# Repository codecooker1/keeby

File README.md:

# keeby
A custom ergonomic split keyboard made for HackClub Blueprint based on Corne, Lily58 and Sofle V2

# Routing PCB
more detailed svg and pdf available in PCB/plot

# Schematic for the right half

# Schematic for the left half

# Casing??
Yup, made the casing in onshape. This is supposed to be 3D printed. You can find the 3D part files in the CAD/PrintParts folder. Here the FullCase is the full 3D model of the casing all parts included. Or you can find 3D models of individual parts in the CAD/PrintParts folder named by part.

Alternatively, you can view the Onshape design here: https://cad.onshape.com/documents/7252c9cab477090fa80b5ebe/w/9b87afb059b10e97f9e15540/e/26e119e6690b400aabda07c5

# How does the final PCB looks?

For detailed view the .step files is in PCB/3dout/

# Final Assembled Keyboard

# Detailed BOM of Keeby

|    | Sourced | Placed | References                                                                                                                                                                                                                                                                                                                                        | Value                | Footprint                               | Description                                                             | Quantity | Unit Price | Total Price | Link                                                                                                                                                                                                                                                                                                                                                                                                                                                                                                                                                                                                                                                                                                                                                                                                                                                                                                                                                                                                                                                                              |
|----|---------|--------|---------------------------------------------------------------------------------------------------------------------------------------------------------------------------------------------------------------------------------------------------------------------------------------------------------------------------------------------------|----------------------|-----------------------------------------|-------------------------------------------------------------------------|----------|------------|-------------|-----------------------------------------------------------------------------------------------------------------------------------------------------------------------------------------------------------------------------------------------------------------------------------------------------------------------------------------------------------------------------------------------------------------------------------------------------------------------------------------------------------------------------------------------------------------------------------------------------------------------------------------------------------------------------------------------------------------------------------------------------------------------------------------------------------------------------------------------------------------------------------------------------------------------------------------------------------------------------------------------------------------------------------------------------------------------------------|
| 1  |         |        | L*                                                           | SK6812MINI-E         | LED_choc_6028R-ROT                      | Reverse mount adressable LED (WS2812 protocol) SK6812-MINI-E            | 58       |            | $6.19       | https://www.aliexpress.com/item/1005007863635868.html?spm=a2g0o.cart.0.0.810538darhu6L5&mp=1&pdp_npi=6%40dis%21USD%21USD%206.19%21USD%206.19%21%21USD%206.19%21%21%21%40212a70c017685672603975784e0c90%2112000042594617264%21ct%21BD%216073142226%21%211%210%21                                                                                                                                                                                                                                                                                                                                                                                                                                                                                                                                                                                                                                                                                                                                                                                                                   |
| 2  |         |        | D*                                                           | D                    | D_SOD-123                               | Diode                                                                   | 100      |            | $0.90       | https://www.aliexpress.com/item/1005005460442161.html?spm=a2g0o.cart.0.0.810538darhu6L5&mp=1&pdp_npi=6%40dis%21USD%21USD%200.98%21USD%200.86%21%21USD%200.86%21%21%21%40212a70c017685672603975784e0c90%2112000033171824002%21ct%21BD%216073142226%21%211%210%21                                                                                                                                                                                                                                                                                                                                                                                                                                                                                                                                                                                                                                                                                                                                                                                                                   |
| 3  |         |        | SW* | SW_Push              | SW_choc_v1_HS_CPG135001S30_1u           | Kailh Choc Mechanical Switch                                            | 70       |            | $21.45      | https://www.aliexpress.com/item/1005008751312031.html?spm=a2g0o.cart.0.0.810538darhu6L5&mp=1&pdp_npi=6%40dis%21USD%21USD%2029.64%21USD%2021.45%21%21USD%2021.45%21%21%21%40212a70c017685672603975784e0c90%2112000046516675121%21ct%21BD%216073142226%21%211%210%21                                                                                                                                                                                                                                                                                                                                                                                                                                                                                                                                                                                                                                                                                                                                                                                                                |
| 4  |         |        | SW59, SW60                                                                                                                                                                                                                                                                                                                                        | RotaryEncoder_Switch | ROT_Alps_EC11E-Switch                   | Rotary encoder, dual channel, incremental quadrate outputs, with switch | 2        | $0.00      | $2.00       | https://www.aliexpress.com/item/1005006136446310.html?spm=a2g0o.cart.0.0.810538darhu6L5&mp=1&pdp_npi=6%40dis%21USD%21USD%200.23%21USD%200.23%21%21USD%200.23%21%21%21%40212a70c017685672603975784e0c90%2112000035923124125%21ct%21BD%216073142226%21%214%210%21                                                                                                                                                                                                                                                                                                                                                                                                                                                                                                                                                                                                                                                                                                                                                                                                                   |
| 5  |         |        | SW61, SW62                                                                                                                                                                                                                                                                                                                                        | SW_SPDT              | SW_SPDT_PCM12                           | Switch, single pole double throw                                        | 2        | $0.50      | $1.00       | https://www.aliexpress.com/item/32951447363.html?spm=a2g0o.productlist.main.9.3fec7a5bb6AoHW&algo_pvid=997ab485-32d4-4ae3-b083-92d8ea070226&algo_exp_id=997ab485-32d4-4ae3-b083-92d8ea070226-8&pdp_ext_f=%7B%22order%22%3A%222%22%2C%22eval%22%3A%221%22%2C%22fromPage%22%3A%22search%22%7D&pdp_npi=6%40dis%21USD%210.50%210.50%21%21%210.50%210.50%21%4021010d9017670062326406800eeead%2112000025562152088%21sea%21BD%216073142226%21ABX%211%210%21n_tag%3A-29910%3Bd%3A3a54dfaf%3Bm03_new_user%3A-29895&curPageLogUid=M9MqK9B1Ixso&utparam-url=scene%3Asearch%7Cquery_from%3A%7Cx_object_id%3A32951447363%7C_p_origin_prod%3A                                                                                                                                                                                                                                                                                                                                                                                                                                                   |
| 6  |         |        | J1, J2                                                                                                                                                                                                                                                                                                                                            | Conn_01x04_Pin       | SSD1306-0.91-OLED-4pin-128x32           | .91" SSD1306 OLED Display                                               | 2        | $1.00      | $2.00       | https://www.alibaba.com/product-detail/0-91-inch-OLED-Module-White_1601154882218.html?chatToken=U1ZkdVJIVkhVRXB3VVd0MVF6QnFTSEJEV21jNEt6SmtiMnBMZWprNGIxVlNlRGRFYm05WmJXa3JlRVZHTDBsUVpFaGpTM0ZXVUdoTmVtbHhNbTg0VWpkbFdrSlFUa292TmtjeVNXSkJTbGtyYzBGS2JsVkJaVzQ1VUZCaFMza3hNMlZEUW1SQlIzSm1NRzFaYW1RMFREbEpTa2hUWW5GRGNXbzVRMGxwWjBjNE0wSm9lREpZVWpKQlNERk5Va05JVFZoS2FtTkVMMlZKVG1WSlJITTRSVGRHYW5SRGJITktaV3BDYkV3MGVuUkJPR0ZFUW1SQ1VUWXdWekpvYmpSTiZ2ZXJzaW9uPTIuMC4w&encryptTargetLoginId=8pctgRBMALNf4b09DmS4sxV0n3wwMjKJ                                                                                                                                                                                                                                                                                                                                                                                                                                                                                                                                                    |
| 7  |         |        | J3, J4                                                                                                                                                                                                                                                                                                                                            | JST_PH               | JST_PH_S2B-PH-K_1x02_P2.00mm_Horizontal | JST Connector for battery                                               | 2        |            | $1.00       | https://www.aliexpress.com/item/4001235017139.html?spm=a2g0o.cart.0.0.810538darhu6L5&mp=1&pdp_npi=6%40dis%21USD%21USD%200.77%21USD%200.73%21%21USD%200.73%21%21%21%40212a70c017685672603975784e0c90%2110000015400386674%21ct%21BD%216073142226%21%211%210%21                                                                                                                                                                                                                                                                                                                                                                                                                                                                                                                                                                                                                                                                                                                                                                                                                      |
| 8  |         |        | N/A                                                                                                                                                                                                                                                                                                                                               | Hotswap Socket       | N/A                                     | Kailh Choc Mechanical Switch Hotswap Socket                             | 58       |            | $7.00       | https://www.aliexpress.com/item/32901654130.html?spm=a2g0o.productlist.main.6.8d11e36aeSUXP9&algo_pvid=a9cd544c-7bcc-4615-bf47-0cada34fa870&algo_exp_id=a9cd544c-7bcc-4615-bf47-0cada34fa870-5&pdp_ext_f=%7B%22order%22%3A%225%22%2C%22eval%22%3A%221%22%2C%22fromPage%22%3A%22search%22%7D&pdp_npi=6%40dis%21USD%211.00%211.00%21%21%211.00%211.00%21%402102f22c17663266103024375e1ee4%2165889444978%21sea%21BD%210%21ABX%211%210%21n_tag%3A-29910%3Bd%3A3bd32eff%3Bm03_new_user%3A-29895&curPageLogUid=v5xv7rZ1f0eT&utparam-url=scene%3Asearch%7Cquery_from%3A%7Cx_object_id%3A32901654130%7C_p_origin_prod%3A                                                                                                                                                                                                                                                                                                                                                                                                                                                                  |
| 9  |         |        | N/A                                                                                                                                                                                                                                                                                                                                               | Choc Keycaps         | N/A                                     | Choc Keycaps Transparent 1u                                             | 70       |            | $14.00      | https://www.aliexpress.com/item/1005010282783838.html?spm=a2g0o.cart.0.0.810538darhu6L5&mp=1&pdp_npi=6%40dis%21USD%21USD%2021.34%21USD%2013.87%21%21USD%2013.87%21%21%21%40212a70c017685672603975784e0c90%2112000051778139004%21ct%21BD%216073142226%21%211%210%21                                                                                                                                                                                                                                                                                                                                                                                                                                                                                                                                                                                                                                                                                                                                                                                                                |
| 10 |         |        | N/A                                                                                                                                                                                                                                                                                                                                               | LiPo Battery         | N/A                                     | LiPo Battries 1200 mAh                                                  | 2        | $1.60      | $3.20       | https://www.daraz.com.bd/products/jst-37v-1200mah-783448-lipo-i447238909-s2140245262.html?c=&channelLpJumpArgs=&clickTrackInfo=query%253Alipo%252Bbattery%252B1200%252BmAh%253Bnid%253A447238909%253Bsrc%253ALazadaMainSrp%253Brn%253A123b02ee72e0153ad0b88c4f2d851919%253Bregion%253Abd%253Bsku%253A447238909_BD%253Bprice%253A189%253Bclient%253Adesktop%253Bsupplier_id%253A1034652%253Bbiz_source%253Ah5_unknow%253Bslot%253A11%253Butlog_bucket_id%253A470687%253Basc_category_id%253A9365%253Bitem_id%253A447238909%253Bsku_id%253A2140245262%253Bshop_id%253A40589%253BtemplateInfo%253A&freeshipping=0&fs_ab=1&fuse_fs=&lang=en&location=Dhaka&price=189&priceCompare=skuId%3A2140245262%3Bsource%3Alazada-search-voucher%3Bsn%3A123b02ee72e0153ad0b88c4f2d851919%3BoriginPrice%3A18900%3BdisplayPrice%3A18900%3BsinglePromotionId%3A-1%3BsingleToolCode%3AmockedSalePrice%3BvoucherPricePlugin%3A0%3Btimestamp%3A1767006835112&ratingscore=4.0&request_id=123b02ee72e0153ad0b88c4f2d851919&review=10&sale=98&search=1&source=search&spm=a2a0e.searchlist.list.11&stock=1 |
| 11 |         |        | U3,U4                                                                                                                                                                                                                                                                                                                                             |                      | SuperMini nRF52840                      | Supermini NRF52840                                                      | 2        | $3.00      | $6.00       | https://www.alibaba.com/product-detail/Promicro-NRF52840-Development-Board-Compatible-with_1601439610830.html?chatToken=U1ZkdVJIVkhVRXB3VVd0MVF6QnFTSEJEV21jNEt6SmtiMnBMZWprNGIxVlNlRGRFYm05WmJXa3JlRzlZU2xoNFZVSjRSV0Y2V0dkTVMyWm1Mell4UTJJclNFeFVaRlkwUW5SelVITnZOWFJyU0hRMU1EVkZWR2N4UkhkSlpGTjNibFJDZEVkVVltZE1LMGREWW1wNmFIZE5VMDl2UTJwcFVHbE9RMlpKSzBaSldUaEVOMVJwV1dkNGEzUlBjMlUxY1haeVVEaEdiMEZaYzFGV05WZFlkRkE1WjFoaE5IbEhjR2hxVkdaSmFFTkllVzF0TWtScVJIbGpkM0JzYW10cyZ2ZXJzaW9uPTIuMC4w&encryptTargetLoginId=8pctgRBMALMgcUFh%2BNBAvYmb4dHbWtMY6wdkfYSa%2Bs4%3D                                                                                                                                                                                                                                                                                                                                                                                                                                                                                                          |
| 12 |         |        | N/A                                                                                                                                                                                                                                                                                                                                               | Choc Keycaps         | N/A                                     | Choc keycaps Black 1.75u                                                | 2        |            | $5.87       | https://www.aliexpress.com/item/1005005916325764.html?spm=a2g0o.productlist.main.23.39c35e7coOVJI8&algo_pvid=714c0d53-c229-474b-a098-63bf297f75e2&algo_exp_id=714c0d53-c229-474b-a098-63bf297f75e2-22&pdp_ext_f={%22order%22%3A%2237%22%2C%22eval%22%3A%221%22%2C%22fromPage%22%3A%22search%22}&pdp_npi=6%40dis!AUD!9.46!1.50!!!6.25!0.99!%402140c1c317668196694054953ee7c0!12000034838215570!sea!AU!0!ABX!1!0!n_tag%3A-29910%3Bd%3A731fdbb5%3Bm03_new_user%3A-29895%3BpisId%3A5000000187462935&curPageLogUid=hfCDIVYR2pPX&utparam-url=scene%3Asearch|query_from%3A|x_object_id%3A1005005916325764|_p_origin_prod%3A                                                                                                                                                                                                                                                                                                                                                                                                                                                              |
|    |         |        |                                                                                                                                                                                                                                                                                                                                                   |                      |                                         |                                                                         | TOTAL    |            | $70.61      |                                                                                                                                                                                                                                                                                                                                                                                                                                                                                                                                                                                                                                                                                                                                                                                                                                                                                                                                                                                                                                                                                   |

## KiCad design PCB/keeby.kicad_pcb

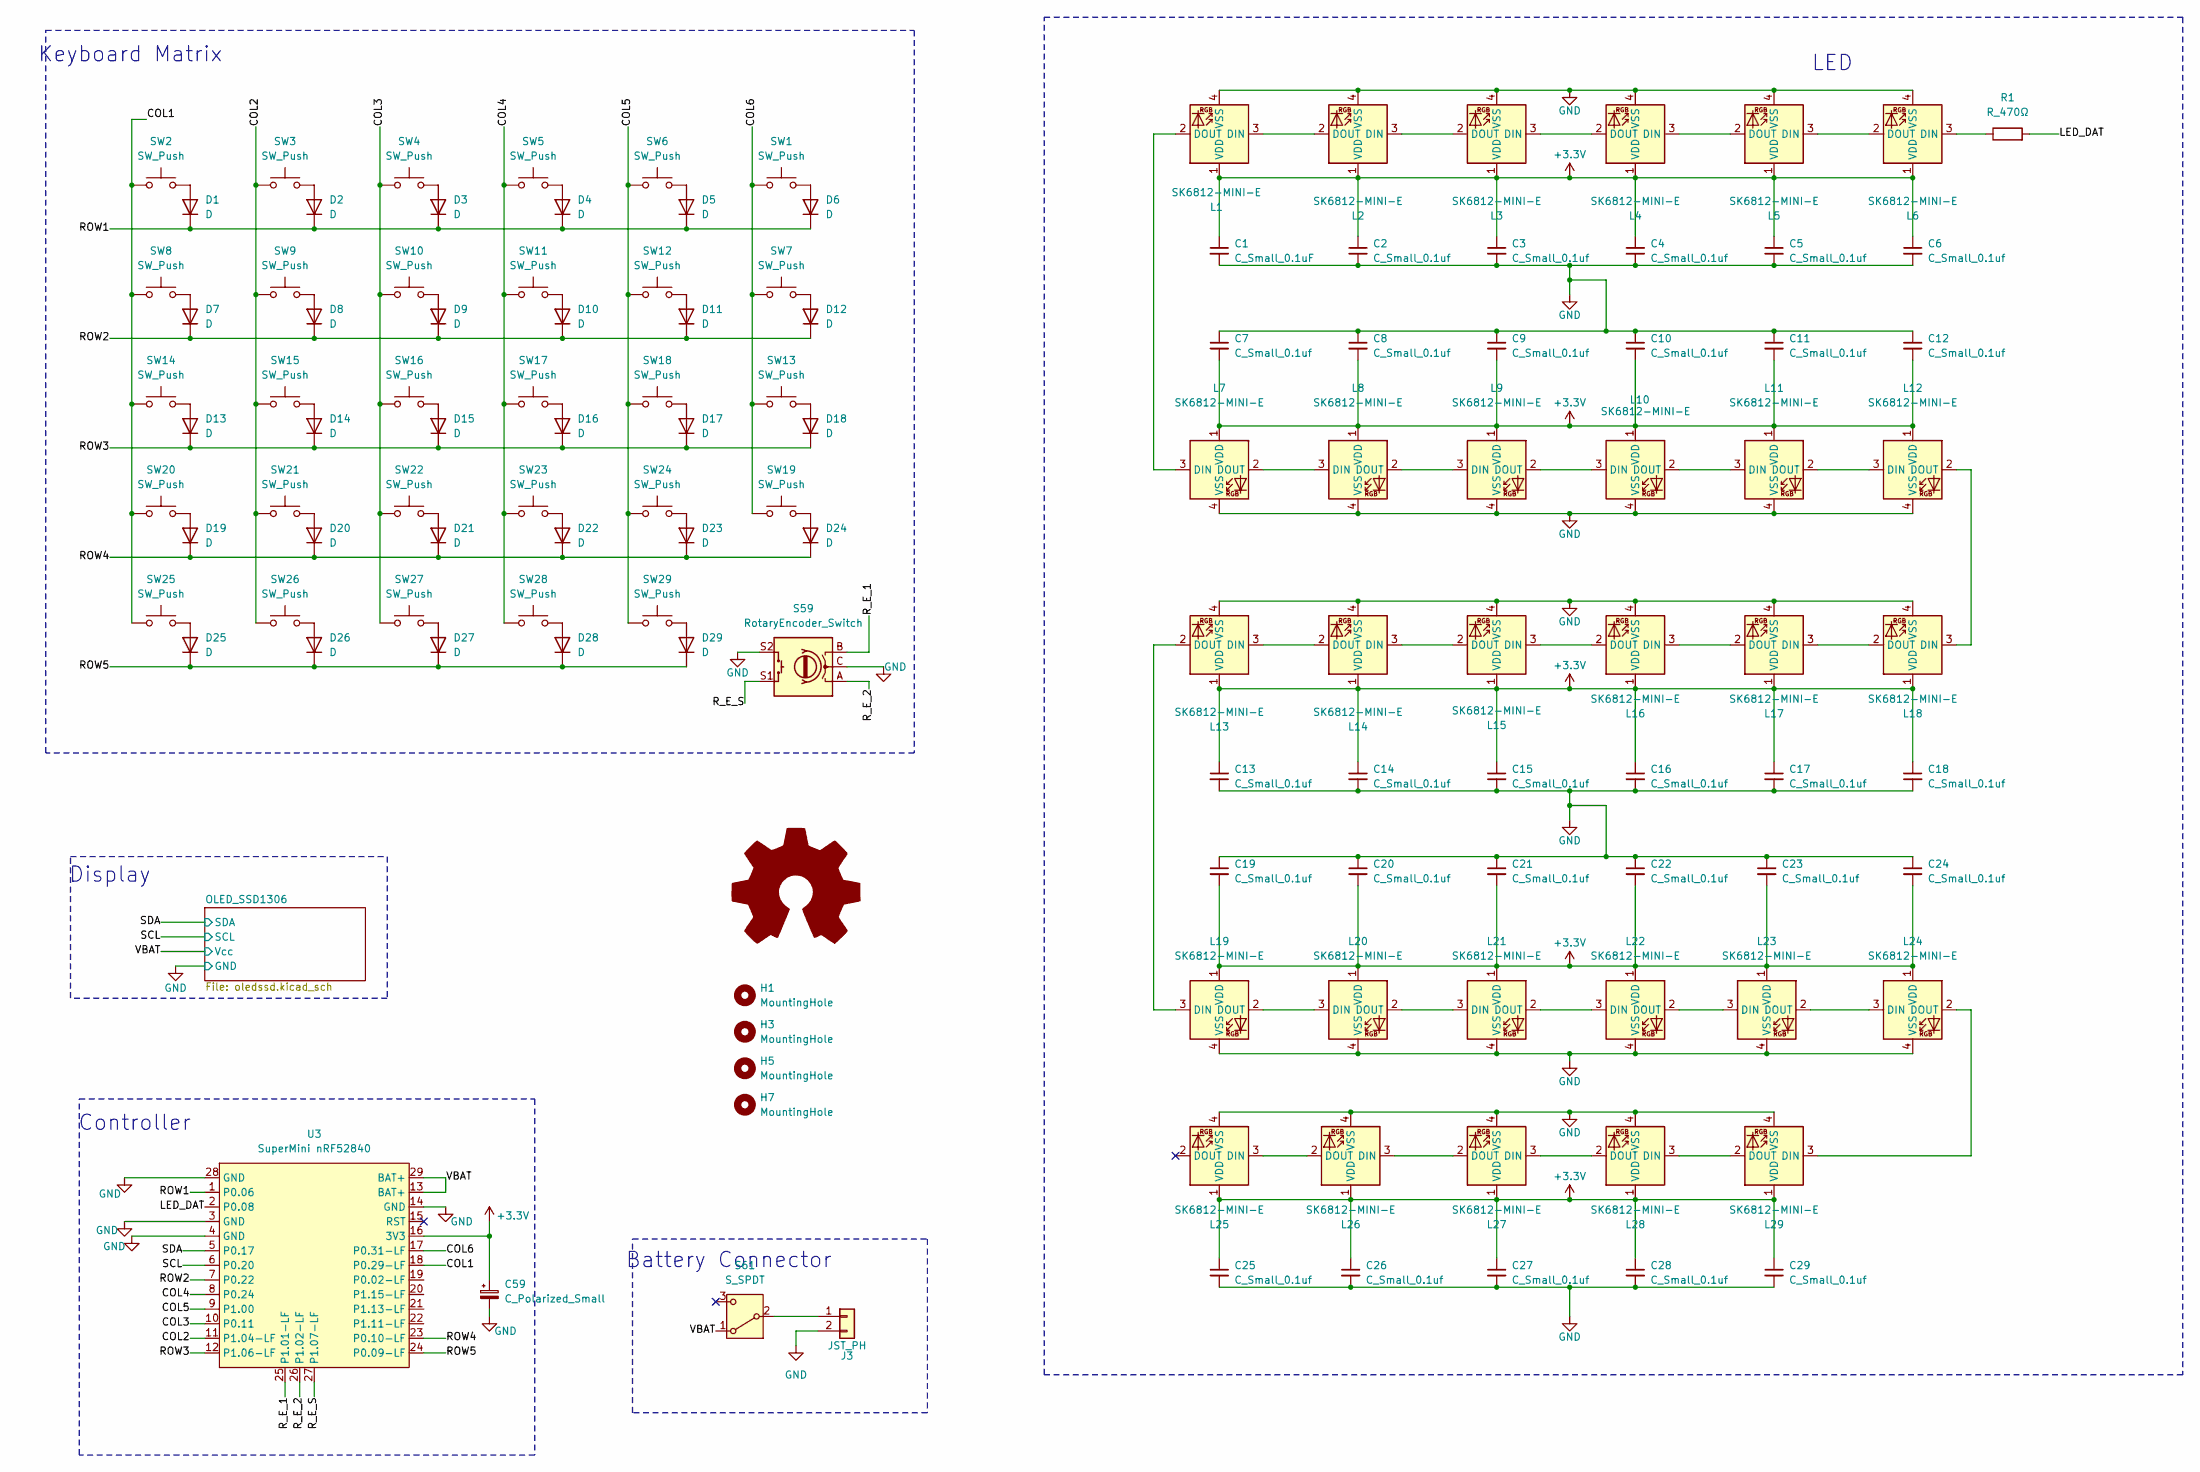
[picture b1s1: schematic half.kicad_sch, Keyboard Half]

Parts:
C1: C_Small_0.1uF; C_0805_2012Metric_Pad1.18x1.45mm_HandSolder
C2, C3, C4, C5, C6, C7, C8, C9, C10, C11, C12, C13, C14, C15, C16, C17, C18, C19, C20, C21, C22, C23, C24, C25, C26, C27, C28, C29: C_Small_0.1uf; C_0805_2012Metric_Pad1.18x1.45mm_HandSolder
C59: C_Polarized_Small; CP_EIA-7343-31_Kemet-D_HandSolder
D1, D2, D3, D4, D5, D6, D7, D8, D9, D10, D11, D12, D13, D14, D15, D16, D17, D18, D19, D20, D21, D22, D23, D24, D25, D26, D27, D28, D29: D; D_SOD-123
H1, H3, H5, H7: MountingHole; MountingHole_2.1mm
J3: JST_PH; JST_PH_S2B-PH-K_1x02_P2.00mm_Horizontal
L1, L2, L3, L4, L5, L6, L7, L8, L9, L10, L11, L12, L13, L14, L15, L16, L17, L18, L19, L20, L21, L22, L23, L24, L25, L26, L27, L28, L29: SK6812-MINI-E; LED_choc_6028R-ROT
R1: R_470Ω; R_0805_2012Metric_Pad1.20x1.40mm_HandSolder
S59: RotaryEncoder_Switch; ROT_Alps_EC11E-Switch
S61: S_SPDT; SW_SPDT_PCM12
SW1, SW2, SW3, SW4, SW5, SW6, SW7, SW8, SW9, SW10, SW11, SW12, SW13, SW14, SW15, SW16, SW17, SW18, SW19, SW20, SW21, SW22, SW23, SW24, SW25, SW26, SW27, SW28, SW29: SW_Push; SW_choc_v1_HS_CPG135001S30_1u
U3: SuperMini nRF52840; SuperMini_nRF52840_AH_USBup

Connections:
+3.3V: C1.1, C2.1, C3.1, C4.1, C5.1, C6.1, C7.2, C8.2, C9.2, C10.2, C11.2, C12.2, C13.1, C14.1, C15.1, C16.1, C17.1, C18.1, C19.2, C20.2, C21.2, C22.2, C23.2, C24.2, C25.1, C26.1, C27.1, C28.1, C29.1, C59.1, L1.1 (VDD), L2.1 (VDD), L3.1 (VDD), L4.1 (VDD), L5.1 (VDD), L6.1 (VDD), L7.1 (VDD), L8.1 (VDD), L9.1 (VDD), L10.1 (VDD), L11.1 (VDD), L12.1 (VDD), L13.1 (VDD), L14.1 (VDD), L15.1 (VDD), L16.1 (VDD), L17.1 (VDD), L18.1 (VDD), L19.1 (VDD), L20.1 (VDD), L21.1 (VDD), L22.1 (VDD), L23.1 (VDD), L24.1 (VDD), L25.1 (VDD), L26.1 (VDD), L27.1 (VDD), L28.1 (VDD), L29.1 (VDD), U3.16 (3V3); also elsewhere on the board
/left/COL1: SW2.1, SW8.1, SW14.1, SW20.1, SW25.1, U3.18 (P0.29-LF)
/left/COL2: SW3.1, SW9.1, SW15.1, SW21.1, SW26.1, U3.11 (P1.04-LF)
/left/COL3: SW4.1, SW10.1, SW16.1, SW22.1, SW27.1, U3.10 (P0.11)
/left/COL4: SW5.1, SW11.1, SW17.1, SW23.1, SW28.1, U3.8 (P0.24)
/left/COL5: SW6.1, SW12.1, SW18.1, SW24.1, SW29.1, U3.9 (P1.00)
/left/COL6: SW1.1, SW7.1, SW13.1, SW19.1, U3.17 (P0.31-LF)
/left/LED_DAT: R1.2, U3.2 (P0.08)
/left/ROW1: D1.1 (K), D2.1 (K), D3.1 (K), D4.1 (K), D5.1 (K), D6.1 (K), U3.1 (P0.06)
/left/ROW2: D7.1 (K), D8.1 (K), D9.1 (K), D10.1 (K), D11.1 (K), D12.1 (K), U3.7 (P0.22)
/left/ROW3: D13.1 (K), D14.1 (K), D15.1 (K), D16.1 (K), D17.1 (K), D18.1 (K), U3.12 (P1.06-LF)
/left/ROW4: D19.1 (K), D20.1 (K), D21.1 (K), D22.1 (K), D23.1 (K), D24.1 (K), U3.23 (P0.10-LF)
/left/ROW5: D25.1 (K), D26.1 (K), D27.1 (K), D28.1 (K), D29.1 (K), U3.24 (P0.09-LF)
/left/R_E_1: S59.B, U3.25 (P1.01-LF)
/left/R_E_2: S59.A, U3.26 (P1.02-LF)
/left/R_E_S: S59.S1, U3.27 (P1.07-LF)
/left/SCL: U3.6 (P0.20); also elsewhere on the board
/left/SDA: U3.5 (P0.17); also elsewhere on the board
/left/VBAT: S61.1 (A), U3.13 (BAT+), U3.29 (BAT+); also elsewhere on the board
GND: C1.2, C2.2, C3.2, C4.2, C5.2, C6.2, C7.1, C8.1, C9.1, C10.1, C11.1, C12.1, C13.2, C14.2, C15.2, C16.2, C17.2, C18.2, C19.1, C20.1, C21.1, C22.1, C23.1, C24.1, C25.2, C26.2, C27.2, C28.2, C29.2, C59.2, J3.2, L1.4 (VSS), L2.4 (VSS), L3.4 (VSS), L4.4 (VSS), L5.4 (VSS), L6.4 (VSS), L7.4 (VSS), L8.4 (VSS), L9.4 (VSS), L10.4 (VSS), L11.4 (VSS), L12.4 (VSS), L13.4 (VSS), L14.4 (VSS), L15.4 (VSS), L16.4 (VSS), L17.4 (VSS), L18.4 (VSS), L19.4 (VSS), L20.4 (VSS), L21.4 (VSS), L22.4 (VSS), L23.4 (VSS), L24.4 (VSS), L25.4 (VSS), L26.4 (VSS), L27.4 (VSS), L28.4 (VSS), L29.4 (VSS), S59.C, S59.S2, U3.3 (GND), U3.4 (GND), U3.14 (GND), U3.28 (GND); also elsewhere on the board
unnamed: D1.2 (A), SW2.2
unnamed: D2.2 (A), SW3.2
unnamed: D3.2 (A), SW4.2
unnamed: D4.2 (A), SW5.2
unnamed: D5.2 (A), SW6.2
unnamed: D6.2 (A), SW1.2
unnamed: D7.2 (A), SW8.2
unnamed: D8.2 (A), SW9.2
unnamed: D9.2 (A), SW10.2
unnamed: D10.2 (A), SW11.2
unnamed: D11.2 (A), SW12.2
unnamed: D12.2 (A), SW7.2
unnamed: D13.2 (A), SW14.2
unnamed: D14.2 (A), SW15.2
unnamed: D15.2 (A), SW16.2
unnamed: D16.2 (A), SW17.2
unnamed: D17.2 (A), SW18.2
unnamed: D18.2 (A), SW13.2
unnamed: D19.2 (A), SW20.2
unnamed: D20.2 (A), SW21.2
unnamed: D21.2 (A), SW22.2
unnamed: D22.2 (A), SW23.2
unnamed: D23.2 (A), SW24.2
unnamed: D24.2 (A), SW19.2
unnamed: D25.2 (A), SW25.2
unnamed: D26.2 (A), SW26.2
unnamed: D27.2 (A), SW27.2
unnamed: D28.2 (A), SW28.2
unnamed: D29.2 (A), SW29.2
unnamed: J3.1, S61.2 (B)
unnamed: L1.3 (DIN), L2.2 (DOUT)
unnamed: L1.2 (DOUT), L7.3 (DIN)
unnamed: L2.3 (DIN), L3.2 (DOUT)
unnamed: L3.3 (DIN), L4.2 (DOUT)
unnamed: L4.3 (DIN), L5.2 (DOUT)
unnamed: L5.3 (DIN), L6.2 (DOUT)
unnamed: L6.3 (DIN), R1.1
unnamed: L7.2 (DOUT), L8.3 (DIN)
unnamed: L8.2 (DOUT), L9.3 (DIN)
unnamed: L9.2 (DOUT), L10.3 (DIN)
unnamed: L10.2 (DOUT), L11.3 (DIN)
unnamed: L11.2 (DOUT), L12.3 (DIN)
unnamed: L12.2 (DOUT), L18.3 (DIN)
unnamed: L13.3 (DIN), L14.2 (DOUT)
unnamed: L13.2 (DOUT), L19.3 (DIN)
unnamed: L14.3 (DIN), L15.2 (DOUT)
unnamed: L15.3 (DIN), L16.2 (DOUT)
unnamed: L16.3 (DIN), L17.2 (DOUT)
unnamed: L17.3 (DIN), L18.2 (DOUT)
unnamed: L19.2 (DOUT), L20.3 (DIN)
unnamed: L20.2 (DOUT), L21.3 (DIN)
unnamed: L21.2 (DOUT), L22.3 (DIN)
unnamed: L22.2 (DOUT), L23.3 (DIN)
unnamed: L23.2 (DOUT), L24.3 (DIN)
unnamed: L24.2 (DOUT), L29.3 (DIN)
unnamed: L25.3 (DIN), L26.2 (DOUT)
unnamed: L26.3 (DIN), L27.2 (DOUT)
unnamed: L27.3 (DIN), L28.2 (DOUT)
unnamed: L28.3 (DIN), L29.2 (DOUT)

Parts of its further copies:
C30, C31, C32, C33, C34, C36, C37, C38, C39, C40, C41, C42, C43, C44, C45, C46, C47, C48, C49, C50, C51, C52, C53, C54, C55, C56, C57, C58: C_Small_0.1uf; C_0805_2012Metric_Pad1.18x1.45mm_HandSolder
C35: C_Small_0.1uF; C_0805_2012Metric_Pad1.18x1.45mm_HandSolder
C60: C_Polarized_Small; CP_EIA-7343-31_Kemet-D_HandSolder
D30, D31, D32, D33, D34, D35, D36, D37, D38, D39, D40, D41, D42, D43, D44, D45, D46, D47, D48, D49, D50, D51, D52, D53, D54, D55, D56, D57, D58: D; D_SOD-123
H2, H4, H6, H8: MountingHole; MountingHole_2.1mm
J4: JST_PH; JST_PH_S2B-PH-K_1x02_P2.00mm_Horizontal
L30, L31, L32, L33, L34, L35, L36, L37, L38, L39, L40, L41, L42, L43, L44, L45, L46, L47, L48, L49, L50, L51, L52, L53, L54, L55, L56, L57, L58: SK6812-MINI-E; LED_choc_6028R-ROT
R2: R_470Ω; R_0805_2012Metric_Pad1.20x1.40mm_HandSolder
S60: RotaryEncoder_Switch; ROT_Alps_EC11E-Switch
S62: S_SPDT; SW_SPDT_PCM12
SW30, SW31, SW32, SW33, SW34, SW35, SW36, SW37, SW38, SW39, SW40, SW41, SW42, SW43, SW44, SW45, SW46, SW47, SW48, SW49, SW50, SW51, SW52, SW53, SW54, SW55, SW56, SW57, SW58: SW_Push; SW_choc_v1_HS_CPG135001S30_1u
U4: SuperMini nRF52840; SuperMini_nRF52840_AH_USBup

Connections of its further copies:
+3.3V: C30.1, C31.1, C32.1, C33.1, C34.1, C35.1, C36.2, C37.2, C38.2, C39.2, C40.2, C41.2, C42.1, C43.1, C44.1, C45.1, C46.1, C47.1, C48.2, C49.2, C50.2, C51.2, C52.2, C53.2, C54.1, C55.1, C56.1, C57.1, C58.1, C60.1, L30.1 (VDD), L31.1 (VDD), L32.1 (VDD), L33.1 (VDD), L34.1 (VDD), L35.1 (VDD), L36.1 (VDD), L37.1 (VDD), L38.1 (VDD), L39.1 (VDD), L40.1 (VDD), L41.1 (VDD), L42.1 (VDD), L43.1 (VDD), L44.1 (VDD), L45.1 (VDD), L46.1 (VDD), L47.1 (VDD), L48.1 (VDD), L49.1 (VDD), L50.1 (VDD), L51.1 (VDD), L52.1 (VDD), L53.1 (VDD), L54.1 (VDD), L55.1 (VDD), L56.1 (VDD), L57.1 (VDD), L58.1 (VDD), U4.16 (3V3); also elsewhere on the board
/right/COL1: SW30.1, SW36.1, SW42.1, SW48.1, SW54.1, U4.18 (P0.29-LF)
/right/COL2: SW31.1, SW37.1, SW43.1, SW49.1, SW55.1, U4.11 (P1.04-LF)
/right/COL3: SW32.1, SW38.1, SW44.1, SW50.1, SW56.1, U4.10 (P0.11)
/right/COL4: SW33.1, SW39.1, SW45.1, SW51.1, SW57.1, U4.8 (P0.24)
/right/COL5: SW34.1, SW40.1, SW46.1, SW52.1, SW58.1, U4.9 (P1.00)
/right/COL6: SW35.1, SW41.1, SW47.1, SW53.1, U4.17 (P0.31-LF)
/right/LED_DAT: R2.2, U4.2 (P0.08)
/right/ROW1: D30.1 (K), D31.1 (K), D32.1 (K), D33.1 (K), D34.1 (K), D35.1 (K), U4.1 (P0.06)
/right/ROW2: D36.1 (K), D37.1 (K), D38.1 (K), D39.1 (K), D40.1 (K), D41.1 (K), U4.7 (P0.22)
/right/ROW3: D42.1 (K), D43.1 (K), D44.1 (K), D45.1 (K), D46.1 (K), D47.1 (K), U4.12 (P1.06-LF)
/right/ROW4: D48.1 (K), D49.1 (K), D50.1 (K), D51.1 (K), D52.1 (K), D53.1 (K), U4.23 (P0.10-LF)
/right/ROW5: D54.1 (K), D55.1 (K), D56.1 (K), D57.1 (K), D58.1 (K), U4.24 (P0.09-LF)
/right/R_E_1: S60.B, U4.25 (P1.01-LF)
/right/R_E_2: S60.A, U4.26 (P1.02-LF)
/right/R_E_S: S60.S1, U4.27 (P1.07-LF)
/right/SCL: U4.6 (P0.20); also elsewhere on the board
/right/SDA: U4.5 (P0.17); also elsewhere on the board
/right/VBAT: S62.1 (A), U4.13 (BAT+), U4.29 (BAT+); also elsewhere on the board
GND: C30.2, C31.2, C32.2, C33.2, C34.2, C35.2, C36.1, C37.1, C38.1, C39.1, C40.1, C41.1, C42.2, C43.2, C44.2, C45.2, C46.2, C47.2, C48.1, C49.1, C50.1, C51.1, C52.1, C53.1, C54.2, C55.2, C56.2, C57.2, C58.2, C60.2, J4.2, L30.4 (VSS), L31.4 (VSS), L32.4 (VSS), L33.4 (VSS), L34.4 (VSS), L35.4 (VSS), L36.4 (VSS), L37.4 (VSS), L38.4 (VSS), L39.4 (VSS), L40.4 (VSS), L41.4 (VSS), L42.4 (VSS), L43.4 (VSS), L44.4 (VSS), L45.4 (VSS), L46.4 (VSS), L47.4 (VSS), L48.4 (VSS), L49.4 (VSS), L50.4 (VSS), L51.4 (VSS), L52.4 (VSS), L53.4 (VSS), L54.4 (VSS), L55.4 (VSS), L56.4 (VSS), L57.4 (VSS), L58.4 (VSS), S60.C, S60.S2, U4.3 (GND), U4.4 (GND), U4.14 (GND), U4.28 (GND); also elsewhere on the board
unnamed: D30.2 (A), SW30.2
unnamed: D31.2 (A), SW31.2
unnamed: D32.2 (A), SW32.2
unnamed: D33.2 (A), SW33.2
unnamed: D34.2 (A), SW34.2
unnamed: D35.2 (A), SW35.2
unnamed: D36.2 (A), SW36.2
unnamed: D37.2 (A), SW37.2
unnamed: D38.2 (A), SW38.2
unnamed: D39.2 (A), SW39.2
unnamed: D40.2 (A), SW40.2
unnamed: D41.2 (A), SW41.2
unnamed: D42.2 (A), SW42.2
unnamed: D43.2 (A), SW43.2
unnamed: D44.2 (A), SW44.2
unnamed: D45.2 (A), SW45.2
unnamed: D46.2 (A), SW46.2
unnamed: D47.2 (A), SW47.2
unnamed: D48.2 (A), SW48.2
unnamed: D49.2 (A), SW49.2
unnamed: D50.2 (A), SW50.2
unnamed: D51.2 (A), SW51.2
unnamed: D52.2 (A), SW52.2
unnamed: D53.2 (A), SW53.2
unnamed: D54.2 (A), SW54.2
unnamed: D55.2 (A), SW55.2
unnamed: D56.2 (A), SW56.2
unnamed: D57.2 (A), SW57.2
unnamed: D58.2 (A), SW58.2
unnamed: J4.1, S62.2 (B)
unnamed: L30.3 (DIN), R2.1
unnamed: L30.2 (DOUT), L31.3 (DIN)
unnamed: L31.2 (DOUT), L32.3 (DIN)
unnamed: L32.2 (DOUT), L33.3 (DIN)
unnamed: L33.2 (DOUT), L34.3 (DIN)
unnamed: L34.2 (DOUT), L35.3 (DIN)
unnamed: L35.2 (DOUT), L41.3 (DIN)
unnamed: L36.3 (DIN), L37.2 (DOUT)
unnamed: L36.2 (DOUT), L42.3 (DIN)
unnamed: L37.3 (DIN), L38.2 (DOUT)
unnamed: L38.3 (DIN), L39.2 (DOUT)
unnamed: L39.3 (DIN), L40.2 (DOUT)
unnamed: L40.3 (DIN), L41.2 (DOUT)
unnamed: L42.2 (DOUT), L43.3 (DIN)
unnamed: L43.2 (DOUT), L44.3 (DIN)
unnamed: L44.2 (DOUT), L45.3 (DIN)
unnamed: L45.2 (DOUT), L46.3 (DIN)
unnamed: L46.2 (DOUT), L47.3 (DIN)
unnamed: L47.2 (DOUT), L53.3 (DIN)
unnamed: L48.3 (DIN), L49.2 (DOUT)
unnamed: L48.2 (DOUT), L54.3 (DIN)
unnamed: L49.3 (DIN), L50.2 (DOUT)
unnamed: L50.3 (DIN), L51.2 (DOUT)
unnamed: L51.3 (DIN), L52.2 (DOUT)
unnamed: L52.3 (DIN), L53.2 (DOUT)
unnamed: L54.2 (DOUT), L55.3 (DIN)
unnamed: L55.2 (DOUT), L56.3 (DIN)
unnamed: L56.2 (DOUT), L57.3 (DIN)
unnamed: L57.2 (DOUT), L58.3 (DIN)

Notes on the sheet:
LED
Display
Controller
Keyboard Matrix
Battery Connector

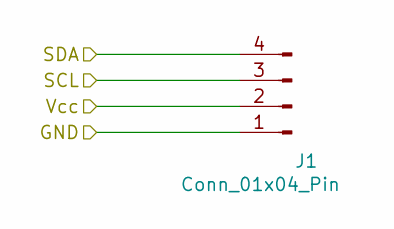
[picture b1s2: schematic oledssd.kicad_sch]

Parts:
J1: Conn_01x04_Pin; SSD1306-0.91-OLED-4pin-128x32

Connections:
/left/SCL: J1.3; also elsewhere on the board
/left/SDA: J1.4; also elsewhere on the board
/left/VBAT: J1.2; also elsewhere on the board
GND: J1.1; also elsewhere on the board

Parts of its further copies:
J2: Conn_01x04_Pin; SSD1306-0.91-OLED-4pin-128x32

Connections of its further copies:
/right/SCL: J2.3; also elsewhere on the board
/right/SDA: J2.4; also elsewhere on the board
/right/VBAT: J2.2; also elsewhere on the board
GND: J2.1; also elsewhere on the board

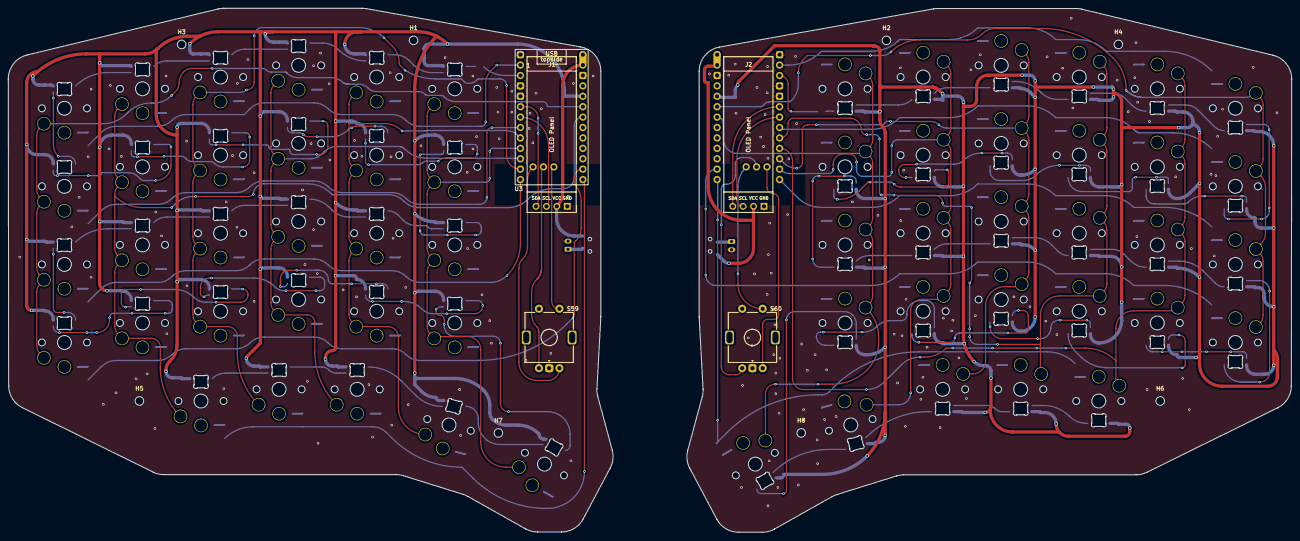
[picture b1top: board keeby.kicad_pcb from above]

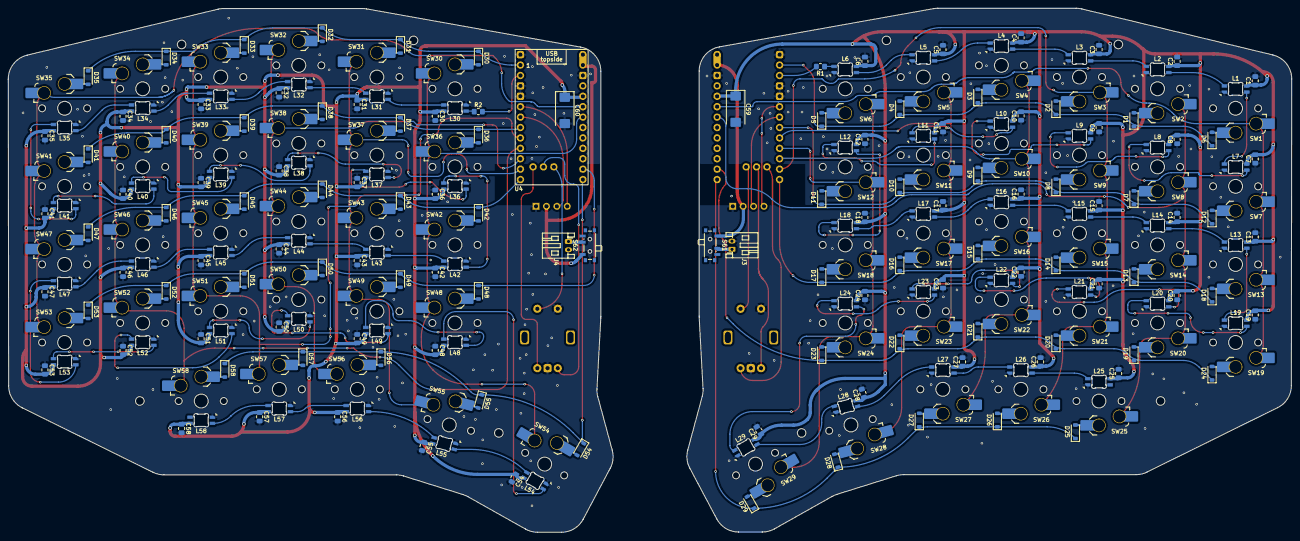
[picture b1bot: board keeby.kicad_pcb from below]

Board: 2 copper layers, 313.2 x 127.9 mm, 254 parts (241 on the bottom side), 156 nets.

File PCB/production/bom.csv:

Designator,Footprint,Quantity,Value,LCSC Part #
"D1, D10, D11, D12, D13, D14, D15, D16, D17, D18, D19, D2, D20, D21, D22, D23, D24, D25, D26, D27, D28, D29, D3, D30, D31, D32, D33, D34, D35, D36, D37, D38, D39, D4, D40, D41, D42, D43, D44, D45, D46, D47, D48, D49, D5, D50, D51, D52, D53, D54, D55, D56, D57, D58, D6, D7, D8, D9",D_SOD-123,58,D,
"J1, J2",SSD1306-0.91-OLED-4pin-128x32,2,Conn_01x04_Pin,
"J3, J4",JST_PH_S2B-PH-K_1x02_P2.00mm_Horizontal,2,JST_PH,
"L1, L10, L11, L12, L13, L14, L15, L16, L17, L18, L19, L2, L20, L21, L22, L23, L24, L25, L26, L27, L28, L29, L3, L30, L31, L32, L33, L34, L35, L36, L37, L38, L39, L4, L40, L41, L42, L43, L44, L45, L46, L47, L48, L49, L5, L50, L51, L52, L53, L54, L55, L56, L57, L58, L6, L7, L8, L9",LED_choc_6028R-ROT,58,SK6812-MINI-E,
"S59, S60",ROT_Alps_EC11E-Switch,2,RotaryEncoder_Switch,
"S61, S62",SW_SPDT_PCM12,2,S_SPDT,
"SW1, SW10, SW11, SW12, SW13, SW14, SW15, SW16, SW17, SW18, SW19, SW2, SW20, SW21, SW22, SW23, SW24, SW25, SW26, SW27, SW28, SW29, SW3, SW30, SW31, SW32, SW33, SW34, SW35, SW36, SW37, SW38, SW39, SW4, SW40, SW41, SW42, SW43, SW44, SW45, SW46, SW47, SW48, SW49, SW5, SW50, SW51, SW52, SW53, SW54, SW55, SW56, SW57, SW58, SW6, SW7, SW8, SW9",SW_choc_v1_HS_CPG135001S30_1u,58,SW_Push,

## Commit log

2025-12-13 First Version?
2025-12-21 test
2025-12-21 fix weird issue
2025-12-21 fix weird permission issue
2025-12-25 start routing
2025-12-27 routed about half
2025-12-27 renamed properly
2025-12-27 placed components
2025-12-27 first route half
2025-12-28 routed
2025-12-29 BOMed
2025-12-29 Updated BOM
2026-01-11 Updated Project Structure
2026-01-11 Fixed Submodules
2026-01-11 cleanup
2026-02-15 Expand README with component sourcing and pricing
    Added detailed component list with sourcing information and pricing.
2026-02-15 cleaning
2026-02-15 add firmware
2026-02-15 Expand README with PCB and BOM details
    Added detailed sections for PCB routing, schematics, casing, and BOM.
2026-03-05 before:
2026-03-10 flipped the switches to be on the right side
2026-03-10 using lfs to track large files >50M
2026-03-11 fixing routing
2026-03-11 switch identifier positioned
2026-03-11 switch aligned with led
2026-03-12 prepare complete redesign
2026-03-12 prepared outline
2026-03-12 started routing
2026-03-12 progress??
2026-03-12 Revert "progress??"
    This reverts commit cc348a77a973bafb10792190f59578297f7118eb.
2026-03-12 progress??2
2026-03-13 fixing leds
2026-03-13 routing
2026-03-13 routed left side
2026-03-13 addes case
2026-03-13 Add CAD documentation for keyboard case
    Added documentation for the keyboard case design in Onshape.
2026-03-13 fixing routing again
2026-03-13 routed left
2026-03-14 routed full
2026-03-15 fixed board
2026-03-17 fixed board + updated README
2026-03-25 added decoupling capacitors
2026-03-26 routed again
2026-03-26 [ImgBot] Optimize images
    *Total -- 14,019.77kb -> 11,087.58kb (20.91%)
    /Pics/keeby-B_Cu.png -- 2,155.06kb -> 1,372.56kb (36.31%)
    /PCB/plot/dxf/keeby-Edge_Cuts.dxf.svg -- 7.64kb -> 5.45kb (28.69%)
    /Pics/keeby-Edge_Cuts.png -- 2,063.35kb -> 1,527.58kb (25.97%)
    /PCB/3dout/keeby.png -- 261.28kb -> 195.27kb (25.26%)
    /Pics/keeby-F_Cu.png -- 1,559.71kb -> 1,176.78kb (24.55%)
2026-03-26 added fully assembled pic of keeby
2026-03-26 Fix HTML encoding in README.md for image tag
2026-04-18 Update BOM for better readibility
